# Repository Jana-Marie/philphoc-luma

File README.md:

# philphoc-luma

Philphoc-luma is a ZigBee (e.g. Philips Hue) to addressable LED-strip (e.g. WS2812, SK6812) bridge. It is based on an E75-2G4M20S and a STM32G030.

## Firmware

There are two firmwares to be flashed, one for the STM32 and one for the E75-2G4M20S.

### ESP32

This is a simple GCC and Make based project, refer to the makefile and use your favourite flasher.

### E75

Please refer to the awesome works of PeeVeeOne to flash Light_ColorLight_JN5168_RGB onto the E75-2G4M20S module.

## License

Copyright Jana Marie Hemsing 2023. This source describes Open Hardware and is licensed under the CERN- OHL-S v2.

You may redistribute and modify this source and make products using it under the terms of the CERN-OHL-S v2 (LICENSE).

This source is distributed WITHOUT ANY EXPRESS OR IMPLIED WARRANTY, INCLUDING OF MERCHANTABILITY, SATISFACTORY QUALITY AND FITNESS FOR A PARTICULAR PURPOSE. Please see the CERN-OHL-S v2 for applicable conditions.

Source location: https://github.com/Jana-Marie/philphoc-luma As per CERN-OHL-S v2 section 4, should You produce hardware based on this source, You must where practicable maintain the Source Location visible on the external case of philphoc-luma or other products you make using this source

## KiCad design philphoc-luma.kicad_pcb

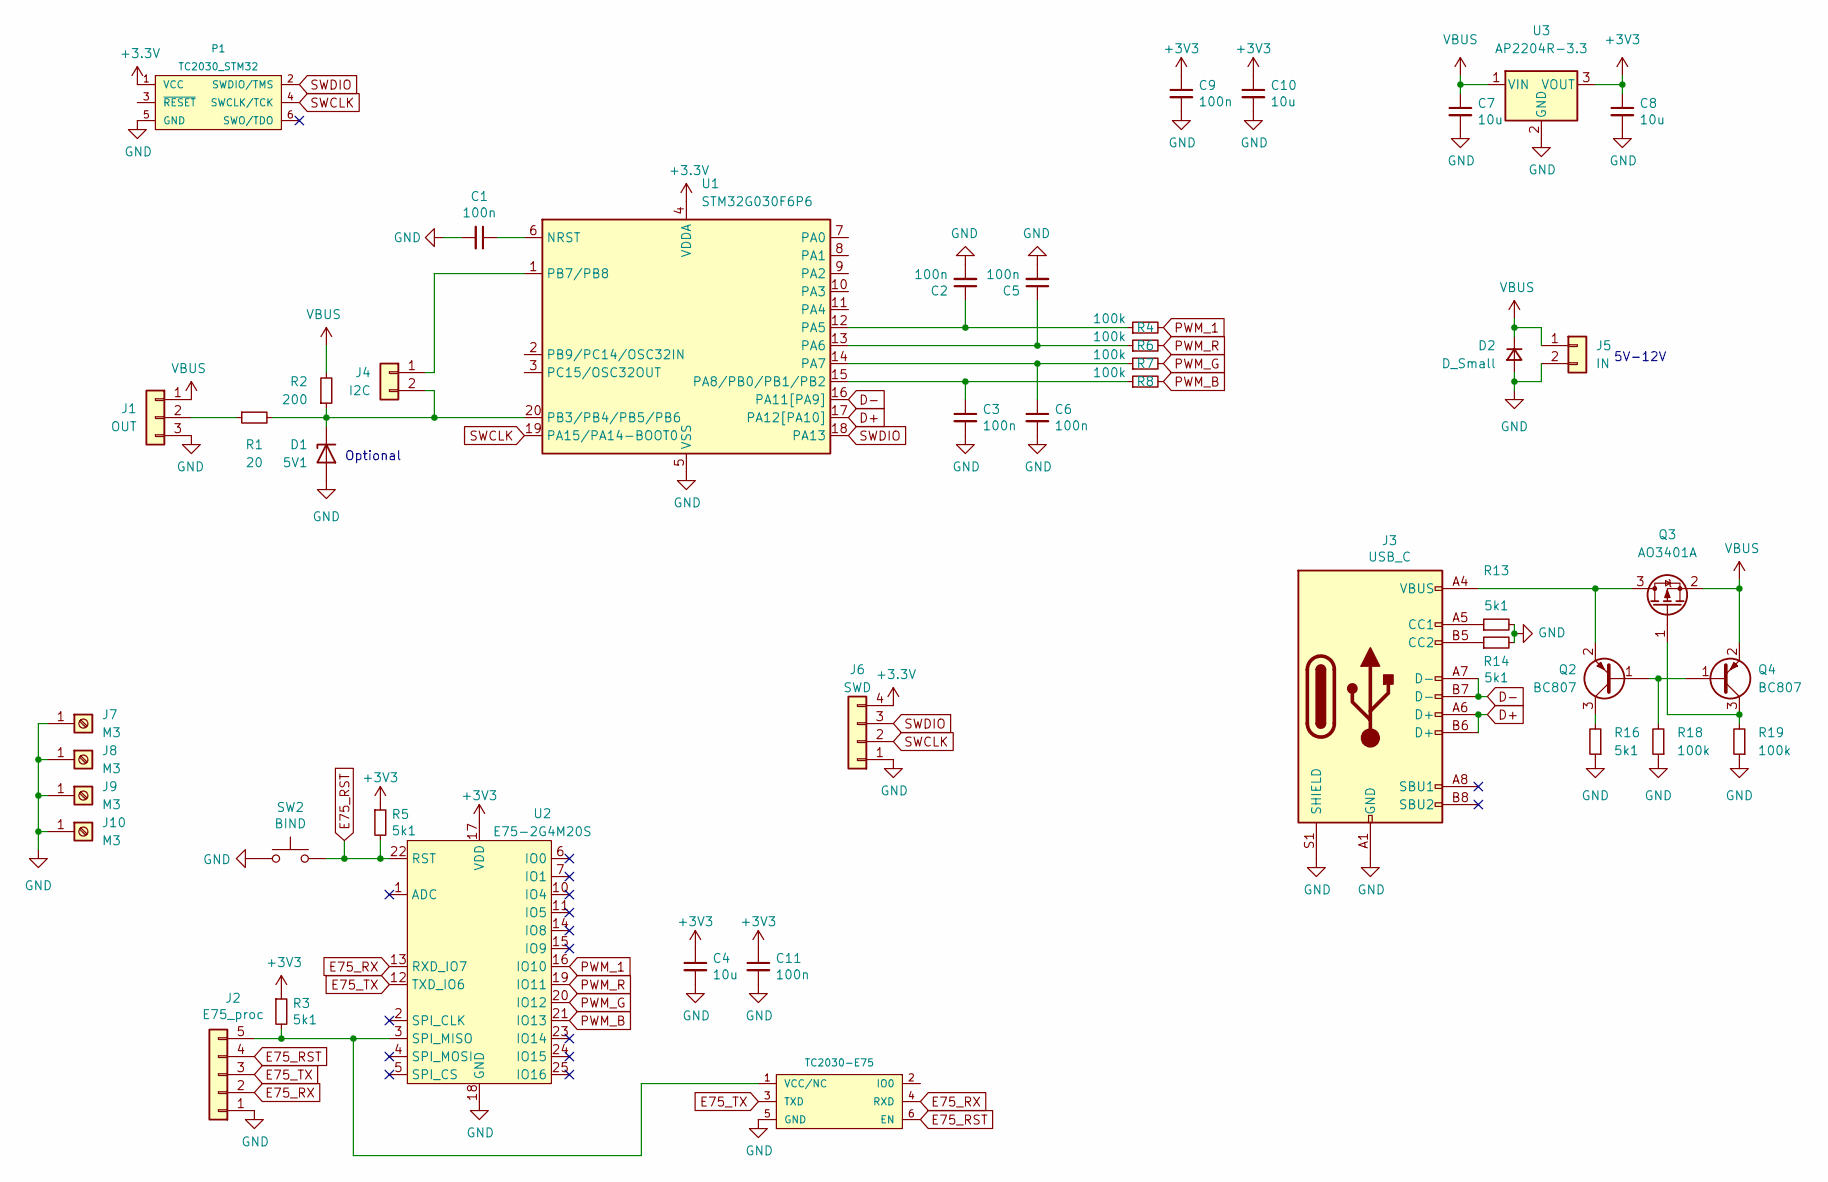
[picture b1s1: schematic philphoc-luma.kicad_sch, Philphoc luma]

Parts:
C1, C2, C3, C5, C6, C9, C11: 100n; C_0402
C4, C7, C8, C10: 10u; C_0603
D1: 5V1; D_SOD-123F
D2: D_Small; D_SOD-123F
J1: OUT; PhoenixContact_MSTBA_2,5_3-G-5,08_1x03_P5.08mm_Horizontal
J2: E75_proc; PinHeader_1x05_P2.54mm_Vertical
J3: USB_C; USB-C 16Pin
J4: I2C; PinHeader_1x02_P2.54mm_Vertical
J5: IN; PhoenixContact_MSTBA_2,5_2-G-5,08_1x02_P5.08mm_Horizontal
J6: SWD; PinSocket_1x04_P2.54mm_Vertical_center
J7, J8, J9, J10: M3; MountingHole_3.2mm_M3_Pad_Via
P1: TC2030_STM32; TC2030
P2: TC2030-E75; TC2030
Q2, Q4: BC807; SOT-23
Q3: AO3401A; SOT-23
R1: 20; R_0402
R2: 200; R_0402
R3, R5, R13, R14, R16: 5k1; R_0402
R4, R6, R7, R8, R18, R19: 100k; R_0402
SW2: BIND; SW_SPST_PTS810
U1: STM32G030F6P6; TSSOP-20_4.4x6.5mm_P0.65mm
U2: E75-2G4M20S; E75-2G4M10S
U3: AP2204R-3.3; SOT-89-3

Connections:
D+: J3.A6 (D+), J3.B6 (D+), U1.17 (PA12[PA10])
D-: J3.A7 (D-), J3.B7 (D-), U1.16 (PA11[PA9])
E75_RST: J2.4, P2.6 (EN), R5.2, SW2.2, U2.22 (RST)
E75_RX: J2.2, P2.4 (RXD), U2.13 (RXD_IO7)
E75_TX: J2.3, P2.3 (TXD), U2.12 (TXD_IO6)
GND: C1.2, C2.2, C3.2, C4.2, C5.2, C6.2, C7.2, C8.2, C9.2, C10.2, C11.2, D1.2 (A), D2.2 (A), J1.3, J2.1, J3.A1 (GND), J3.A12 (GND), J3.B1 (GND), J3.B12 (GND), J3.S1 (SHIELD), J5.2, J6.1, J7.1, J8.1, J9.1, J10.1, P1.5 (GND), P2.5 (GND), R13.2, R14.2, R16.1, R18.1, R19.1, SW2.1, U1.5 (VSS), U2.18 (GND), U3.2 (GND)
unnamed: C1.1, U1.6 (NRST)
unnamed: C2.1, R4.1, U1.12 (PA5)
unnamed: C3.1, R8.1, U1.15 (PA8/PB0/PB1/PB2)
unnamed: C5.1, R6.1, U1.13 (PA6)
unnamed: C6.1, R7.1, U1.14 (PA7)
unnamed: D1.1 (K), J4.2, R1.2, R2.1, U1.20 (PB3/PB4/PB5/PB6)
unnamed: J1.2, R1.1
unnamed: J2.5, P2.1 (VCC/NC), R3.2, U2.3 (SPI_MISO)
unnamed: J3.A4 (VBUS), J3.A9 (VBUS), J3.B4 (VBUS), J3.B9 (VBUS), Q2.2 (E), Q3.3 (D)
unnamed: J3.A5 (CC1), R13.1
unnamed: J3.B5 (CC2), R14.1
unnamed: J4.1, U1.1 (PB7/PB8)
unnamed: Q2.1 (B), Q4.1 (B), R18.2
unnamed: Q2.3 (C), R16.2
unnamed: Q3.1 (G), Q4.3 (C), R19.2
PWM_1: R4.2, U2.16 (IO10)
PWM_B: R8.2, U2.21 (IO13)
PWM_G: R7.2, U2.20 (IO12)
PWM_R: R6.2, U2.19 (IO11)
SWCLK: J6.2, P1.4 (SWCLK/TCK), U1.19 (PA15/PA14-BOOT0)
SWDIO: J6.3, P1.2 (SWDIO/TMS), U1.18 (PA13)
VBUS: C7.1, D2.1 (K), J1.1, J5.1, Q3.2 (S), Q4.2 (E), R2.2, U3.1 (VIN)

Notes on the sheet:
Optional
5V-12V

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
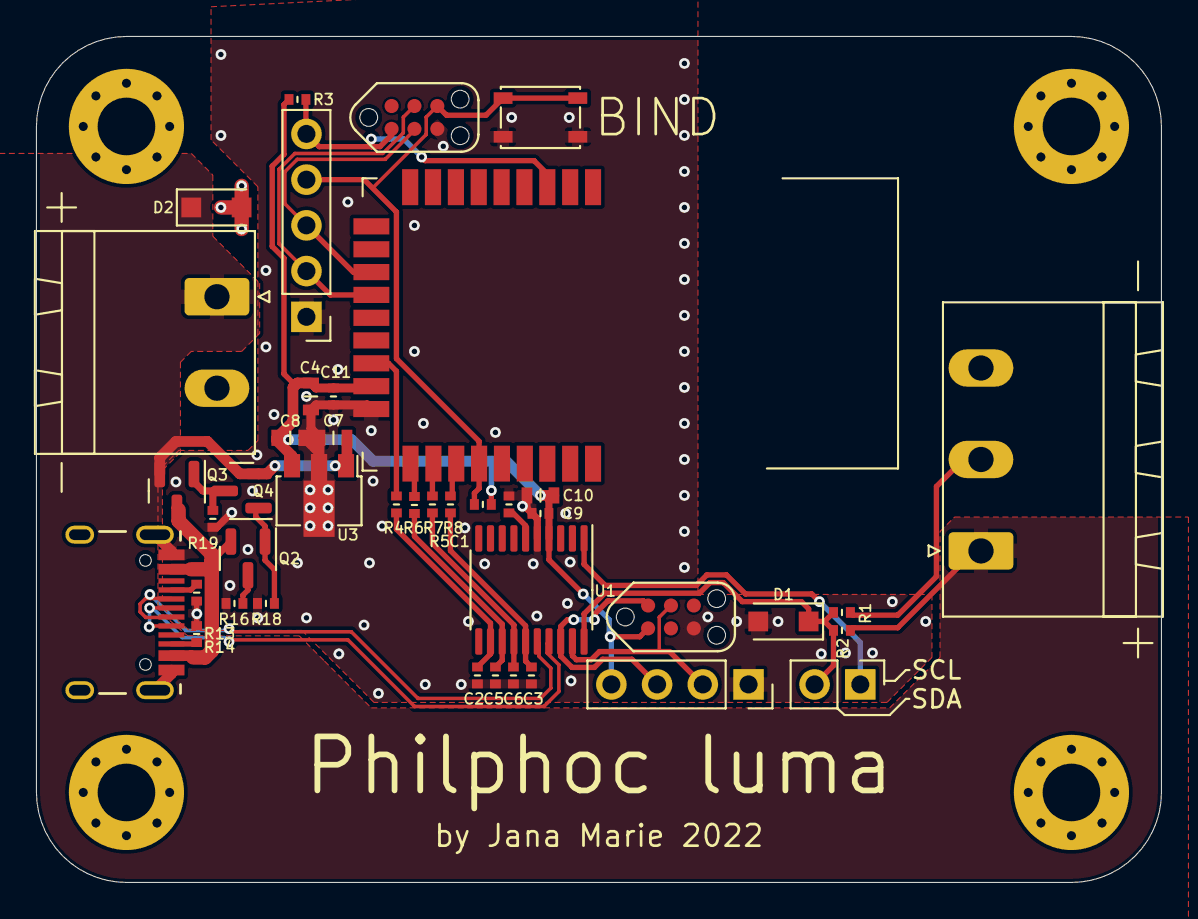
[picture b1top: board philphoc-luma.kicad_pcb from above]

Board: 2 copper layers, 62.5 x 47.0 mm, 45 parts (0 on the bottom side), 29 nets.

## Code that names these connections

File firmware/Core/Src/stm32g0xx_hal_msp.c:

/* USER CODE BEGIN Header */
/**
  ******************************************************************************
  * @file         stm32g0xx_hal_msp.c
  * @brief        This file provides code for the MSP Initialization
  *               and de-Initialization codes.
  ******************************************************************************
  * @attention
  *
  * <h2><center>&copy; Copyright (c) 2022 STMicroelectronics.
  * All rights reserved.</center></h2>
  *
  * This software component is licensed by ST under BSD 3-Clause license,
  * the "License"; You may not use this file except in compliance with the
  * License. You may obtain a copy of the License at:
  *                        opensource.org/licenses/BSD-3-Clause
  *
  ******************************************************************************
  */
/* USER CODE END Header */

/* Includes ------------------------------------------------------------------*/
#include "main.h"
/* USER CODE BEGIN Includes */

/* USER CODE END Includes */

/* Private typedef -----------------------------------------------------------*/
/* USER CODE BEGIN TD */

/* USER CODE END TD */

/* Private define ------------------------------------------------------------*/
/* USER CODE BEGIN Define */

/* USER CODE END Define */

/* Private macro -------------------------------------------------------------*/
/* USER CODE BEGIN Macro */

/* USER CODE END Macro */

/* Private variables ---------------------------------------------------------*/
/* USER CODE BEGIN PV */

/* USER CODE END PV */

/* Private function prototypes -----------------------------------------------*/
/* USER CODE BEGIN PFP */

/* USER CODE END PFP */

/* External functions --------------------------------------------------------*/
/* USER CODE BEGIN ExternalFunctions */

/* USER CODE END ExternalFunctions */

/* USER CODE BEGIN 0 */

/* USER CODE END 0 */
/**
  * Initializes the Global MSP.
  */
void HAL_MspInit(void)
{
  /* USER CODE BEGIN MspInit 0 */

  /* USER CODE END MspInit 0 */

  __HAL_RCC_SYSCFG_CLK_ENABLE();
  __HAL_RCC_PWR_CLK_ENABLE();

  /* System interrupt init*/

  /* USER CODE BEGIN MspInit 1 */

  /* USER CODE END MspInit 1 */
}

/**
* @brief ADC MSP Initialization
* This function configures the hardware resources used in this example
* @param hadc: ADC handle pointer
* @retval None
*/
void HAL_ADC_MspInit(ADC_HandleTypeDef* hadc)
{
  GPIO_InitTypeDef GPIO_InitStruct = {0};
  RCC_PeriphCLKInitTypeDef PeriphClkInit = {0};
  if(hadc->Instance==ADC1)
  {
  /* USER CODE BEGIN ADC1_MspInit 0 */

  /* USER CODE END ADC1_MspInit 0 */

  /** Initializes the peripherals clocks
  */
    PeriphClkInit.PeriphClockSelection = RCC_PERIPHCLK_ADC;
    PeriphClkInit.AdcClockSelection = RCC_ADCCLKSOURCE_SYSCLK;
    if (HAL_RCCEx_PeriphCLKConfig(&PeriphClkInit) != HAL_OK)
    {
      Error_Handler();
    }

    /* Peripheral clock enable */
    __HAL_RCC_ADC_CLK_ENABLE();

    __HAL_RCC_GPIOA_CLK_ENABLE();
    __HAL_RCC_GPIOB_CLK_ENABLE();
    /**ADC1 GPIO Configuration
    PA5     ------> ADC1_IN5
    PA6     ------> ADC1_IN6
    PA7     ------> ADC1_IN7
    PB0     ------> ADC1_IN8
    */
    GPIO_InitStruct.Pin = GPIO_PIN_5|GPIO_PIN_6|GPIO_PIN_7;
    GPIO_InitStruct.Mode = GPIO_MODE_ANALOG;
    GPIO_InitStruct.Pull = GPIO_NOPULL;
    HAL_GPIO_Init(GPIOA, &GPIO_InitStruct);

    GPIO_InitStruct.Pin = GPIO_PIN_0;
    GPIO_InitStruct.Mode = GPIO_MODE_ANALOG;
    GPIO_InitStruct.Pull = GPIO_NOPULL;
    HAL_GPIO_Init(GPIOB, &GPIO_InitStruct);

  /* USER CODE BEGIN ADC1_MspInit 1 */

  /* USER CODE END ADC1_MspInit 1 */
  }

}

/**
* @brief ADC MSP De-Initialization
* This function freeze the hardware resources used in this example
* @param hadc: ADC handle pointer
* @retval None
*/
void HAL_ADC_MspDeInit(ADC_HandleTypeDef* hadc)
{
  if(hadc->Instance==ADC1)
  {
  /* USER CODE BEGIN ADC1_MspDeInit 0 */

  /* USER CODE END ADC1_MspDeInit 0 */
    /* Peripheral clock disable */
    __HAL_RCC_ADC_CLK_DISABLE();

    /**ADC1 GPIO Configuration
    PA5     ------> ADC1_IN5
    PA6     ------> ADC1_IN6
    PA7     ------> ADC1_IN7
    PB0     ------> ADC1_IN8
    */
    HAL_GPIO_DeInit(GPIOA, GPIO_PIN_5|GPIO_PIN_6|GPIO_PIN_7);

    HAL_GPIO_DeInit(GPIOB, GPIO_PIN_0);

  /* USER CODE BEGIN ADC1_MspDeInit 1 */

  /* USER CODE END ADC1_MspDeInit 1 */
  }

}

/**
* @brief SPI MSP Initialization
* This function configures the hardware resources used in this example
* @param hspi: SPI handle pointer
* @retval None
*/
void HAL_SPI_MspInit(SPI_HandleTypeDef* hspi)
{
  GPIO_InitTypeDef GPIO_InitStruct = {0};
  if(hspi->Instance==SPI1)
  {
  /* USER CODE BEGIN SPI1_MspInit 0 */

  /* USER CODE END SPI1_MspInit 0 */
    /* Peripheral clock enable */
    __HAL_RCC_SPI1_CLK_ENABLE();

    __HAL_RCC_GPIOA_CLK_ENABLE();
    __HAL_RCC_GPIOB_CLK_ENABLE();
    /**SPI1 GPIO Configuration
    PA1     ------> SPI1_SCK
    PB5     ------> SPI1_MOSI
    */
    GPIO_InitStruct.Pin = GPIO_PIN_1;
    GPIO_InitStruct.Mode = GPIO_MODE_AF_PP;
    GPIO_InitStruct.Pull = GPIO_NOPULL;
    GPIO_InitStruct.Speed = GPIO_SPEED_FREQ_LOW;
    GPIO_InitStruct.Alternate = GPIO_AF0_SPI1;
    HAL_GPIO_Init(GPIOA, &GPIO_InitStruct);

    GPIO_InitStruct.Pin = GPIO_PIN_5;
    GPIO_InitStruct.Mode = GPIO_MODE_AF_OD;
    GPIO_InitStruct.Pull = GPIO_NOPULL;
    GPIO_InitStruct.Speed = GPIO_SPEED_FREQ_HIGH;
    GPIO_InitStruct.Alternate = GPIO_AF0_SPI1;
    HAL_GPIO_Init(GPIOB, &GPIO_InitStruct);

  /* USER CODE BEGIN SPI1_MspInit 1 */

  /* USER CODE END SPI1_MspInit 1 */
  }

}

/**
* @brief SPI MSP De-Initialization
* This function freeze the hardware resources used in this example
* @param hspi: SPI handle pointer
* @retval None
*/
void HAL_SPI_MspDeInit(SPI_HandleTypeDef* hspi)
{
  if(hspi->Instance==SPI1)
  {
  /* USER CODE BEGIN SPI1_MspDeInit 0 */

  /* USER CODE END SPI1_MspDeInit 0 */
    /* Peripheral clock disable */
    __HAL_RCC_SPI1_CLK_DISABLE();

    /**SPI1 GPIO Configuration
    PA1     ------> SPI1_SCK
    PB5     ------> SPI1_MOSI
    */
    HAL_GPIO_DeInit(GPIOA, GPIO_PIN_1);

    HAL_GPIO_DeInit(GPIOB, GPIO_PIN_5);

  /* USER CODE BEGIN SPI1_MspDeInit 1 */

  /* USER CODE END SPI1_MspDeInit 1 */
  }

}

/**
* @brief TIM_Base MSP Initialization
* This function configures the hardware resources used in this example
* @param htim_base: TIM_Base handle pointer
* @retval None
*/
void HAL_TIM_Base_MspInit(TIM_HandleTypeDef* htim_base)
{
  if(htim_base->Instance==TIM3)
  {
  /* USER CODE BEGIN TIM3_MspInit 0 */

  /* USER CODE END TIM3_MspInit 0 */
    /* Peripheral clock enable */
    __HAL_RCC_TIM3_CLK_ENABLE();
    /* TIM3 interrupt Init */
    HAL_NVIC_SetPriority(TIM3_IRQn, 0, 0);
    HAL_NVIC_EnableIRQ(TIM3_IRQn);
  /* USER CODE BEGIN TIM3_MspInit 1 */

  /* USER CODE END TIM3_MspInit 1 */
  }

}

/**
* @brief TIM_Base MSP De-Initialization
* This function freeze the hardware resources used in this example
* @param htim_base: TIM_Base handle pointer
* @retval None
*/
void HAL_TIM_Base_MspDeInit(TIM_HandleTypeDef* htim_base)
{
  if(htim_base->Instance==TIM3)
  {
  /* USER CODE BEGIN TIM3_MspDeInit 0 */

  /* USER CODE END TIM3_MspDeInit 0 */
    /* Peripheral clock disable */
    __HAL_RCC_TIM3_CLK_DISABLE();

    /* TIM3 interrupt DeInit */
    HAL_NVIC_DisableIRQ(TIM3_IRQn);
  /* USER CODE BEGIN TIM3_MspDeInit 1 */

  /* USER CODE END TIM3_MspDeInit 1 */
  }

}

/* USER CODE BEGIN 1 */

/* USER CODE END 1 */

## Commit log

2022-03-23 added kicad files
2022-03-23 added schematic pdf
2022-03-24 exchanged STM32f030 for STM32G030
2022-03-24 exchanged fw generator file
2022-03-24 updated gerber
2022-11-24 added gitignore
2022-11-24 added fw
2022-11-24 removed files
2022-11-27 updated gitignore
2022-11-27 removed old files
2022-11-27 updated firmware
2022-11-27 updated sch
2022-11-27 created rendering
2022-11-27 added license
2022-11-27 Fixed README.md
2023-03-07 updated fws
